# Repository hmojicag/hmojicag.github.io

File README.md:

## Welcome to Hazael site

in order to contribute follow this steps:

1. clone the repo
1. install ruby and jekyll following this page [Jekyll](https://jekyllrb.com/docs/windows/)
1. cd into the repo
1. `bundle install`
1. `bundle exec jekyll serve`

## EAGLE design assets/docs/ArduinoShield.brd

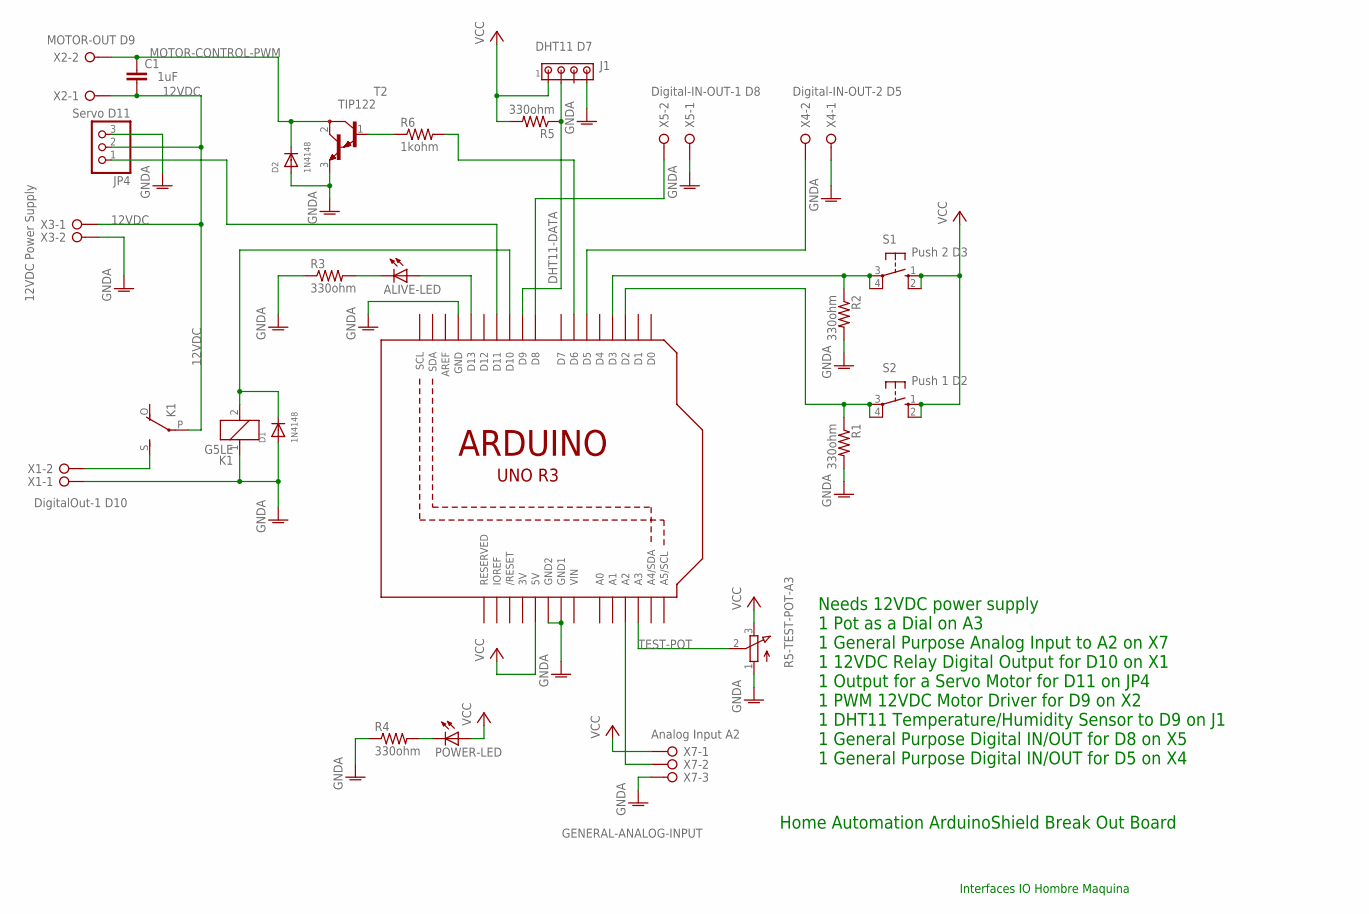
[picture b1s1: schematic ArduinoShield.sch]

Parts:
ALIVE-LED: LED5MM
C1: 1uF; C5B3
D1, D2: 1N4148; DO-1N4148
J1: DHT11 D7; 10X04MTA
JP4: Servo D11; 1X03
K1: G5LE
POWER-LED: LED5MM
R1, R2, R3, R4, R5: 330ohm; 0204/7
R5-TEST-POT-A3: 3RP/1610N
R6: 1kohm; 0204/7
S1: Push 2 D3; B3F-10XX
S2: Push 1 D2; B3F-10XX
T2: TIP122; TO220
U1: ARDUINOR3-DIMENSION; ARDUINOR3
X1, X3, X4, X5: W237-02P; W237-132
X2: MOTOR-OUT D9; W237-132
X7: GENERAL-ANALOG-INPUT; W237-133

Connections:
3V: U1.3V
12VDC: C1.2, JP4.2, K1.P, X2.1, X3.1
DHT11-DATA: J1.2, R5.1, U1.D9
GNDA: D1.A, D2.A, J1.4, JP4.3, K1.1, R1.2, R2.2, R3.1, R4.1, R5-TEST-POT-A3.1 (A), T2.3 (E), U1.GND, U1.GND1, U1.GND2, X1.1, X3.2, X4.1, X5.1, X7.3
MOTOR-CONTROL-PWM: C1.1, D2.C, T2.2 (C), X2.2
unnamed: U1.A2, X7.2
unnamed: ALIVE-LED.A, U1.D13
unnamed: U1.D5, X4.2
unnamed: JP4.1, U1.D11
unnamed: R2.1, S1.3, S1.4 (P1), U1.D3
unnamed: R1.1, S2.3, S2.4 (P1), U1.D2
unnamed: ALIVE-LED.K (C), R3.2
unnamed: D1.C, K1.2, U1.D10
unnamed: K1.S, X1.2
unnamed: POWER-LED.K (C), R4.2
unnamed: R6.2, U1.D6
unnamed: R6.1, T2.1 (B)
unnamed: U1.D8, X5.2
TEST-POT: R5-TEST-POT-A3.2 (S), U1.A3
VCC: J1.1, POWER-LED.A, R5.2, R5-TEST-POT-A3.3 (E), S1.1 (S), S1.2 (S1), S2.1 (S), S2.2 (S1), U1.5V, X7.1
VIN: U1.VIN

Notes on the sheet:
Interfaces IO Hombre Maquina
Home Automation ArduinoShield Break Out Board
Needs 12VDC power supply 1 Pot as a Dial on A3 1 General Purpose Analog Input to A2 on X7 1 12VDC Relay Digital Output for D10 on X1 1 Output for a Servo Motor for D11 on JP4 1 PWM 12VDC Motor Driver for D9 on X2 1 DHT11 Temperature/Humidity Sensor to D9 on J1 1 General Purpose Digital IN/OUT for D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
DigitalOut-1 D10
12VDC Power Supply
Digital-IN-OUT-1 D8
Analog Input A2
Digital-IN-OUT-2 D5

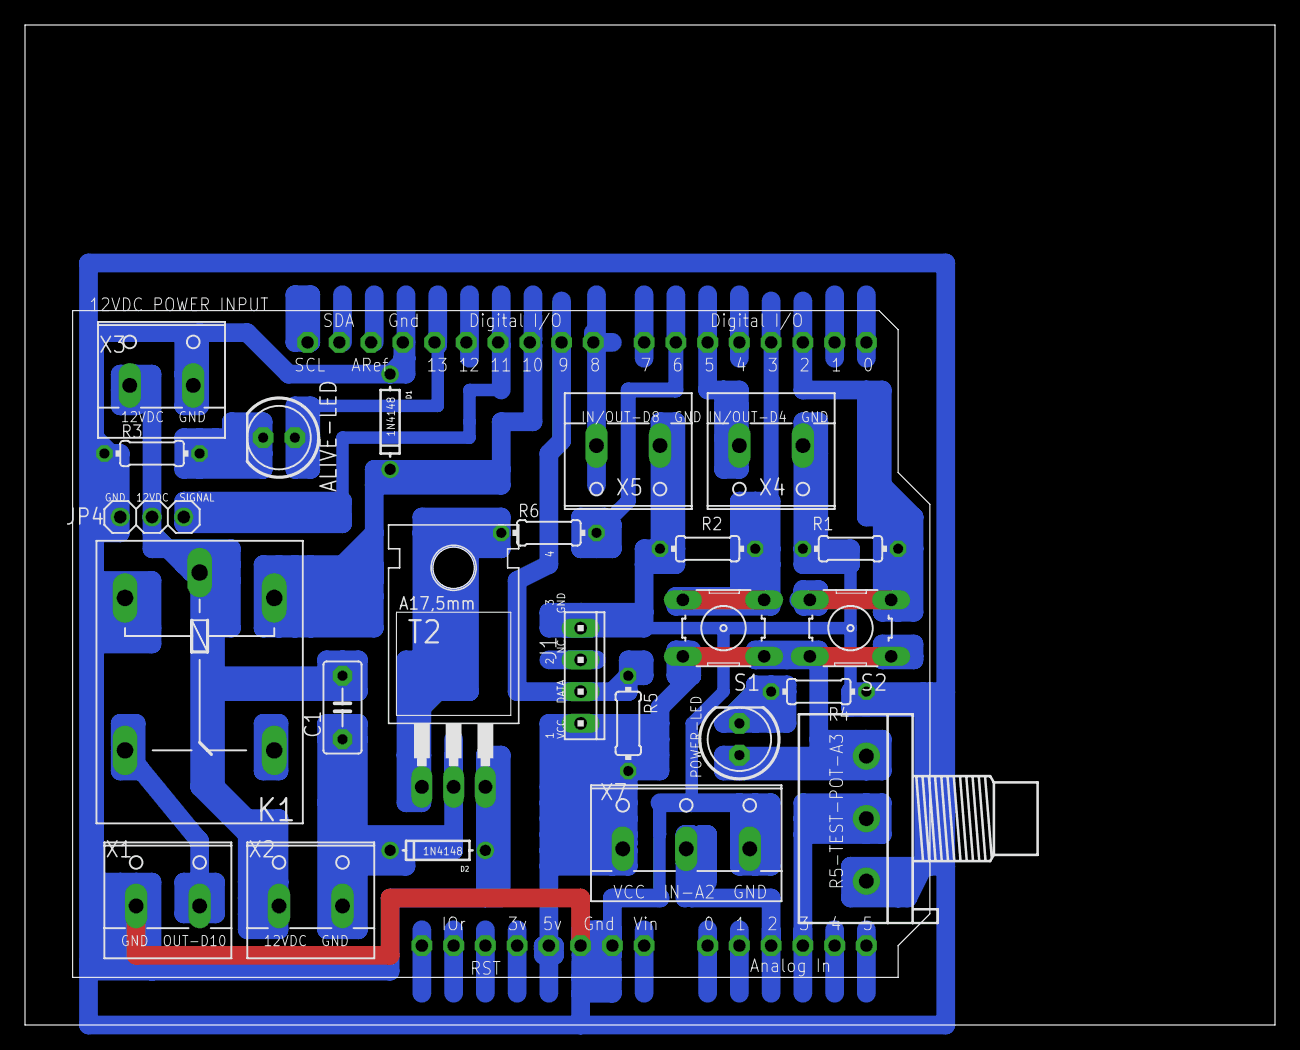
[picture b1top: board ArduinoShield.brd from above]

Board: 2 copper layers, 100.0 x 80.0 mm, 25 parts (0 on the bottom side), 19 nets.

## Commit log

2017-03-30 Adding index page
2017-03-30 adding stuff
2017-03-30 adding more stuff
2017-04-01 My first repo
2017-04-08 JS Example
2017-05-12 Set theme jekyll-theme-hacker
2017-05-12 Al final comprendi esta mmda de Jekyll
2017-05-12 Getting familiar with the jekyll structure
2017-05-13 Starting seriously with the HMI course
2017-05-14 Finishing writting on HMI 1
2017-06-02 Starting HMI 2
2017-06-07 Continue wirking on HMI 2
2017-06-07 Adding code image
2017-06-08 Adding Disquss to the site
2017-06-09 Adding example Arduino IO Multi
2017-06-12 Starting with The Serial Port
2017-06-13 Starting Serial com example
2017-06-26 Almost finishing 3 last examples
2017-06-26 Ending with HMI 2
2017-06-28 Adding Arduino Serial reference
2017-06-30 arreglando lo de haza :P
2017-06-30 deleting gemfile.lock
2017-06-30 arreglando lo mio
2017-07-01 Fixing led interval on Arduino Multi IO
2017-07-01 stupid pins
2017-07-01 Rewording
2017-07-22 hmi1-esp
2017-07-31 Rename spanish folder and make some changes
2017-08-07 Starting HMI3 and editing index files
2017-08-07 Fixing broken link
2017-08-11 My First File
2017-08-11 Adding FB group
2017-08-11 Fucking index.html
2017-08-14 Finish with HMI3
2017-08-14 Adding GitHub link to HMI3 Ex2
2017-08-14 Changing case named images
2017-08-14 Adding FB Group to index HMI
2017-08-19 Fixing Exception in HMI3 Ex2
2017-08-19 Better image
2017-08-24 HMI4
2017-08-24 fixing
2017-08-28 HMI4 adding video
2017-08-28 .md missing
2017-10-09 Adding hmi5 and hmi6
2017-10-10 Adding BOM
2017-10-10 adding fb page
2017-10-10 dummy
2017-10-10 dummy2
2017-10-16 Sharing Course Material (books and shit)
2017-10-24 New version
2017-10-25 Updating again the board
2017-10-25 uploading latest sch
2017-10-31 Adding schematics
2017-10-31 adding demo image
2017-10-31 fixing image name
2018-01-24 calendario 2018
2018-01-26 update calendar
2018-05-17 Generating page for final project
2018-05-17 adding to index
2018-05-17 Adding up to 5 videos
2018-05-17 more videos
2018-05-18 Adding rest of the videos
2018-05-22 Adding link to final project
2018-07-31 Updating for semester Ago - Dic 2018
2018-08-07 test for first online lecture
2018-08-07 Online Lecture 1
2018-08-08 Adding video 2
2018-08-09 Adding Online Lecture 3
2018-08-10 Adding slides to Online Lectures 1 to 3
2018-08-14 Adding Online Lecture 4
2018-08-20 Online Lecture 5
2018-08-24 Finishing up Online Lecture 6
2018-08-24 jum, it failed maybe because of this
2018-08-24 Adding a link to index progra web
2018-08-28 OnlineLecture 7
2018-08-28 Online Lecture 8
2018-08-28 Adding online lecture 8 to index
2018-08-28 OnlineLecture 9
2018-09-02 Online Lectures 10 an 11
2018-09-02 Fixing shit
2019-01-23 Updating calendar
2019-01-24 Replacing gb group link with whatsapp group link
2019-02-18 Adding comic
2019-02-23 Adding images
2019-02-25 testing with bootstrap
2019-02-25 Test1
2019-02-25 Last touches to 1
2019-02-25 No content
2019-02-25 transcript
2019-02-25 Moving transcript and tags to page content
2019-02-25 Fixing typos
2019-02-26 Adding 2
2019-03-07 Adding aass 3
2019-03-07 Fixing links
2019-03-07 Fixing images
2019-03-07 Only render if not empty
2019-03-11 Adding 4
2019-03-11 fixing 4
2019-03-20 adding 5
2019-03-20 adding 6 skeleton
2019-03-21 Adding 6 and 7
2019-03-26 Adding 8
2019-03-26 8 typo
2019-03-26 Adding 9
2019-03-29 just starting
2019-03-29 Automating a bunch of stuff
2019-04-04 Add 10
2019-04-04 comic count 10
2019-04-18 Adding 11
2019-05-26 Starting with api workshop
2019-05-27 Finishing Session 1
2019-05-27 Starting session 1
2019-05-27 Adding image http
2019-05-27 Adding some images
2019-05-27 continuing session 2
2019-05-28 I think I finished session 2
2019-06-07 collapsible test
2019-06-07 test collapsible
2019-06-07 Session 3 almost done
2019-06-12 sessions 3 and 4
2019-06-13 Finishing up session 4
2019-06-13 Adding appdbcontext session3
2019-07-13 Workshop web development
2019-07-13 Adding bullets
2019-07-24 Adding link for workshop-web-development sample code
2019-07-29 Adding _posts/2019-07-29-Cookie_Base_Authentication_in_ASP_Net_Core.md
2019-07-29 Adding some links
2019-07-29 Forgot to add login.cshtml
2019-07-29 change markdown of code cshtml to html lets see if it works
2019-08-02 Type in aass 9
2019-08-06 Adding ago dic 2019
2019-10-04 Starting with 12
2020-01-13 Updating to enero - junio 2020
2020-04-14 Adding 12
2020-08-05 Adding sicam
2020-08-10 No uber
2020-08-10 Adding break line
2020-08-10 Reformatting
2020-08-10 Adding solucion ilegal
2020-09-01 Updating hmi
2020-09-01 Updating progra web
2021-06-17 Adding blog entry for SSH Tunnel SQL Server connection
2021-06-21 Adding more info to post, like error msg
2021-11-30 Removing ass from index
2022-10-17 Enabling AASS back
2024-04-09 Removing AASS, it was not even a good comic
2026-02-25 Updating Index
